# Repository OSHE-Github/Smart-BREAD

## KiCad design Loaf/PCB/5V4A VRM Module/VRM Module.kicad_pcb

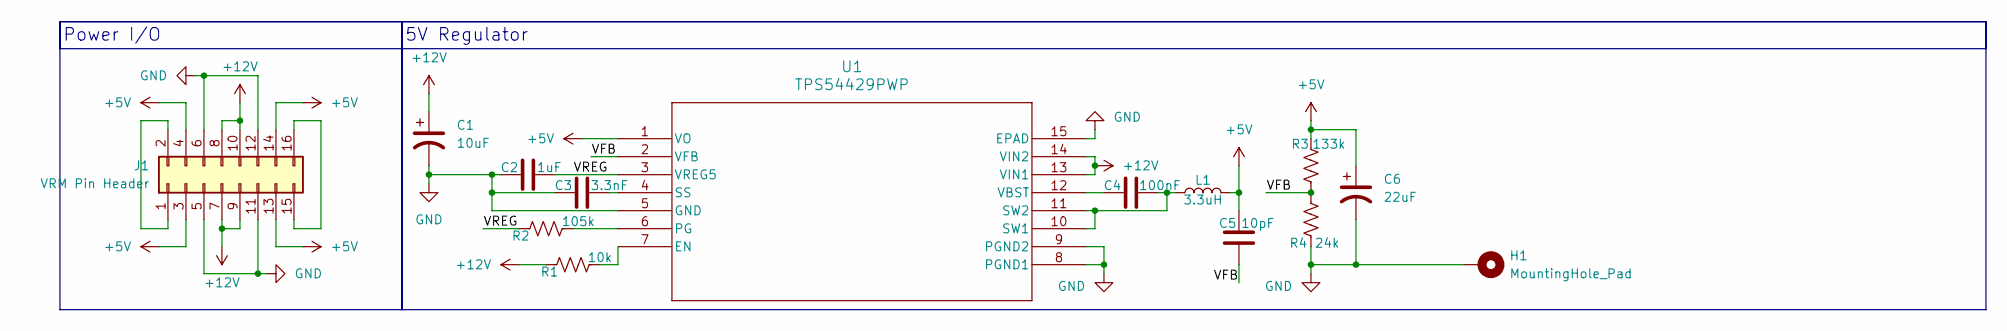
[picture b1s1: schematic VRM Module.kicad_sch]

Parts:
C1: 10uF; CP_Radial_D5.0mm_P2.50mm
C2: 1uF; C_1206_3216Metric_Pad1.33x1.80mm_HandSolder
C3: 3.3nF; C_1206_3216Metric_Pad1.33x1.80mm_HandSolder
C4: 100nF; C_1206_3216Metric_Pad1.33x1.80mm_HandSolder
C5: 10pF; C_1206_3216Metric_Pad1.33x1.80mm_HandSolder
C6: 22uF; CP_Radial_D5.0mm_P2.50mm
H1: MountingHole_Pad; MountingHole_3.2mm_M3_DIN965_Pad
J1: VRM Pin Header; PinHeader_2x08_P2.54mm_Vertical
L1: 3.3uH; R_1206_3216Metric_Pad1.30x1.75mm_HandSolder
R1: 10k; R_1206_3216Metric_Pad1.30x1.75mm_HandSolder
R2: 105k; R_1206_3216Metric_Pad1.30x1.75mm_HandSolder
R3: 133k; R_1206_3216Metric_Pad1.30x1.75mm_HandSolder
R4: 24k; R_1206_3216Metric_Pad1.30x1.75mm_HandSolder
U1: TPS54429PWP; Texas_HTSSOP-14-1EP_4.4x5mm_P0.65mm_EP3.4x5mm_Mask2.94x3.34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

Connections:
+5V: C5.2, C6.1, J1.3, J1.4, J1.13, J1.14, L1.2, R3.2, U1.1 (VO)
+12V: C1.1, J1.7, J1.8, J1.9, J1.10, R1.1, U1.13 (VIN1), U1.14 (VIN2)
/VFB: C5.1, R3.1, R4.2, U1.2 (VFB)
/VREG: C2.2, R2.1, U1.3 (VREG5)
GND: C1.2, C2.1, C3.1, C6.2, H1.1 (1_1), J1.5, J1.6, J1.11, J1.12, R4.1, U1.5 (GND), U1.8 (PGND1), U1.9 (PGND2), U1.15 (EPAD)
unnamed: J1.1, J1.2
unnamed: J1.15, J1.16
unnamed: R1.2, U1.7 (EN)
unnamed: R2.2, U1.6 (PG)
unnamed: C3.2, U1.4 (SS)
unnamed: C4.2, L1.1, U1.10 (SW1), U1.11 (SW2)
unnamed: C4.1, U1.12 (VBST)

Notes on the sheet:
5V Regulator
Power I/O

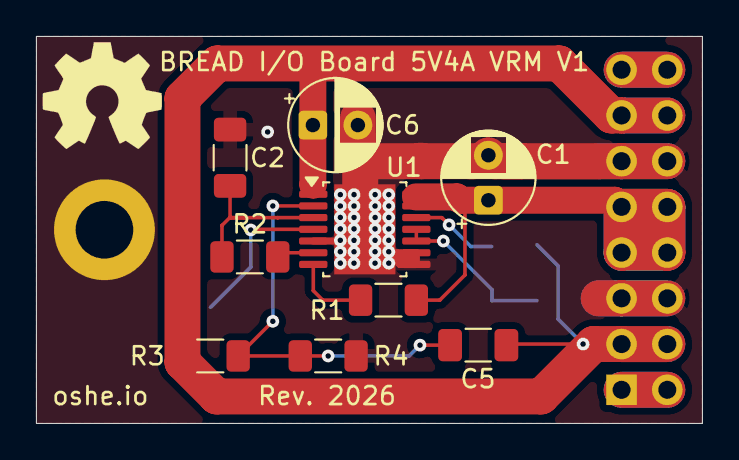
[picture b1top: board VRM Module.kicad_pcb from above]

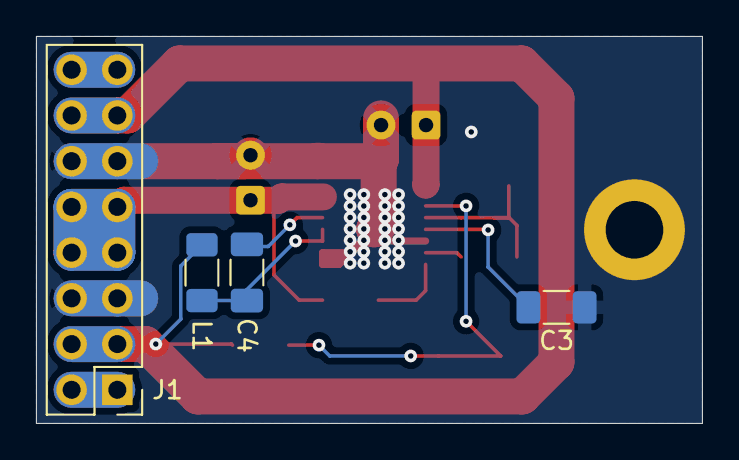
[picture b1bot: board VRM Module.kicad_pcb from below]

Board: 2 copper layers, 37.0 x 21.5 mm, 15 parts (5 on the bottom side), 12 nets.

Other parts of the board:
Logo1: Logo_Open_Hardware_Small; OSHW-Symbol_6.7x6mm_SilkScreen

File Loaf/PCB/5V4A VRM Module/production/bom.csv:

Designator,Footprint,Quantity,Value,LCSC Part #
C1,CP_Radial_D5.0mm_P2.50mm,1,10uF,
C2,1206,1,1uF,
C3,1206,1,3.3uF,
C4,1206,1,100nF,
C5,1206,1,10pF,
C6,CP_Radial_D5.0mm_P2.50mm,1,22uF,
J1,PinHeader_2x08_P2.54mm_Vertical,1,VRM Pin Header,
L1,1206,1,3.3uH,
LOGO1,OSHW-Symbol_6.7x6mm_SilkScreen,1,Logo_Open_Hardware_Small,
R1,1206,1,10k,
R2,1206,1,105k,
R3,1206,1,133k,
R4,1206,1,24k,
U1,Texas_HTSSOP-14-1EP_4.4x5mm_P0.65mm_EP3.4x5mm_Mask2.94x3.34mm,1,TPS54429PWP,

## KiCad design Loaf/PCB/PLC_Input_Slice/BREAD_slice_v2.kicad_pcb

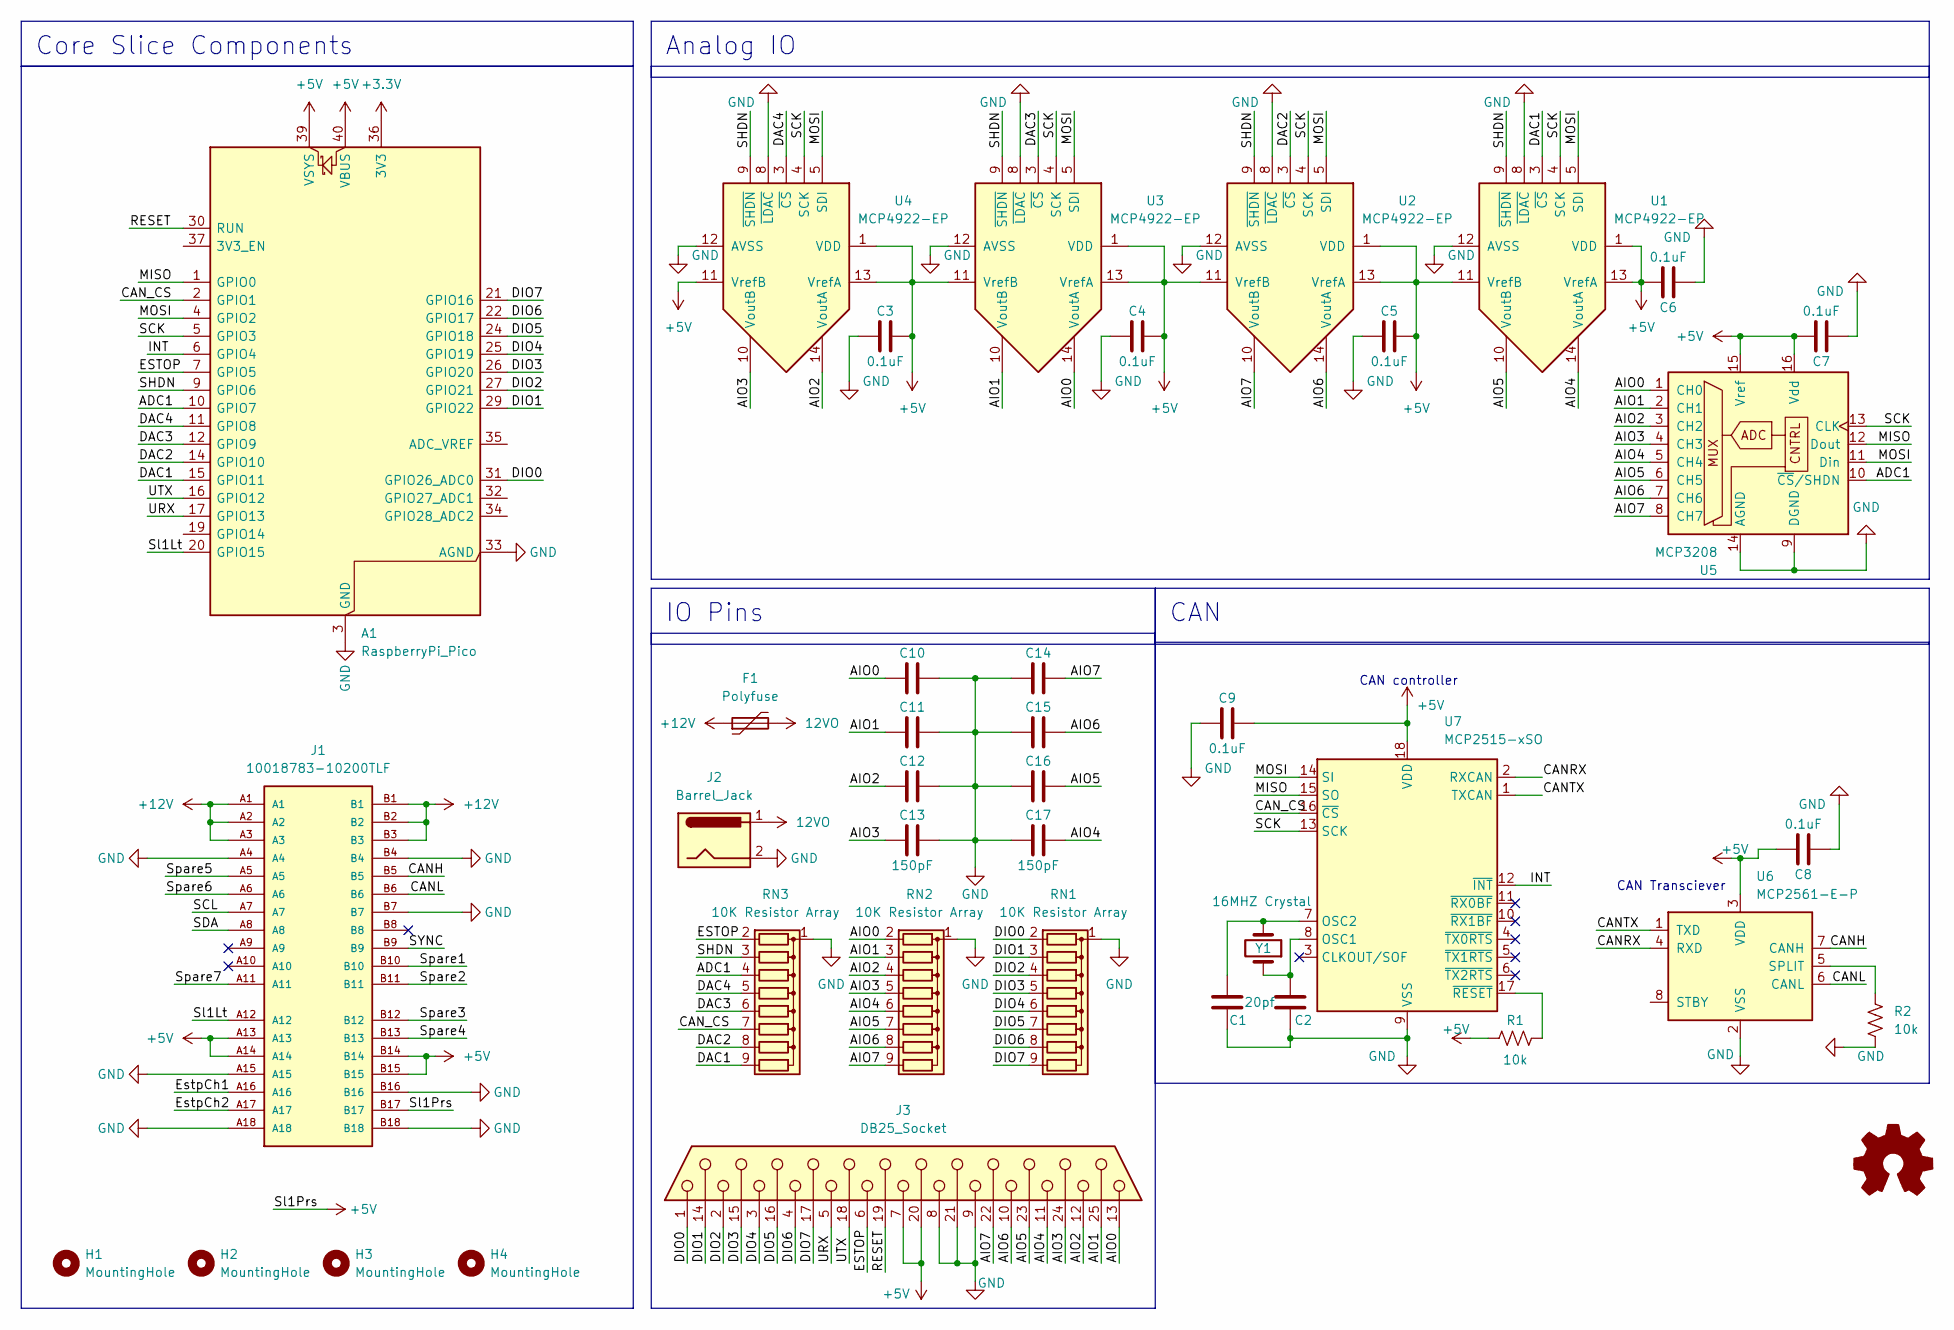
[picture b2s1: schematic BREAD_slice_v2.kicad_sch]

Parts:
A1: RaspberryPi_Pico; RaspberryPi_Pico_Common_Unspecified
C1, C2: 20pf; C_1206_3216Metric_Pad1.33x1.80mm_HandSolder
C3, C4, C5, C6, C7, C8, C9: 0.1uF; C_1206_3216Metric_Pad1.33x1.80mm_HandSolder
C10, C11, C12, C13, C14, C15, C16, C17: 150pF; C_1206_3216Metric_Pad1.33x1.80mm_HandSolder
F1: Polyfuse; Fuse_2920_7451Metric_Pad2.10x5.45mm_HandSolder
H1, H2, H3, H4: MountingHole; MountingHole_3.2mm_M3_DIN965_Pad
J1: 10018783-10200TLF; BUS_PCIexpress_x1; PARTREV Z
J2: Barrel_Jack; BarrelJack_CUI_PJ-063AH_Horizontal
J3: DB25_Socket; DSUB-25_Socket_Horizontal_P2.77x2.84mm_EdgePinOffset4.94mm_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
Logo1: Logo_Open_Hardware_Small; OSHW-Symbol_6.7x6mm_SilkScreen
R1, R2: 10k; R_1206_3216Metric_Pad1.30x1.75mm_HandSolder
RN1, RN2, RN3: 10K Resistor Array; R_Array_SIP9
U1, U2, U3, U4: MCP4922-EP; DIP-14_W7.62mm
U5: MCP3208; DIP-16_W7.62mm_LongPads
U6: MCP2561-E-P; DIP-8_W7.62mm
U7: MCP2515-xSO; DIP-18_W7.62mm
Y1: 16MHZ Crystal; Crystal_HC49-4H_Vertical

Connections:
12VO: F1.2, J2.1
+3.3V: A1.36 (3V3)
+5V: A1.39 (VSYS), A1.40 (VBUS), C3.2, C4.2, C5.2, C6.2, C7.2, C8.2, C9.2, J1.A13, J1.A14, J1.B14, J1.B15, J1.B17, J3.7, J3.20, R1.2, U1.1 (VDD), U1.11 (VrefB), U1.13 (VrefA), U2.1 (VDD), U2.11 (VrefB), U2.13 (VrefA), U3.1 (VDD), U3.11 (VrefB), U3.13 (VrefA), U4.1 (VDD), U4.11 (VrefB), U4.13 (VrefA), U5.15 (Vref), U5.16 (Vdd), U6.3 (VDD), U7.18 (VDD)
+12V: F1.1, J1.A1, J1.A2, J1.A3, J1.B1, J1.B2, J1.B3
/ADC1: A1.10 (GPIO7), RN3.4 (R3), U5.10 (~CS/SHDN)
/AIO0: C10.1, J3.13, RN2.2 (R1), U3.14 (VoutA), U5.1 (CH0)
/AIO1: C11.1, J3.25, RN2.3 (R2), U3.10 (VoutB), U5.2 (CH1)
/AIO2: C12.1, J3.12, RN2.4 (R3), U4.14 (VoutA), U5.3 (CH2)
/AIO3: C13.1, J3.24, RN2.5 (R4), U4.10 (VoutB), U5.4 (CH3)
/AIO4: C17.2, J3.11, RN2.6 (R5), U1.14 (VoutA), U5.5 (CH4)
/AIO5: C16.2, J3.23, RN2.7 (R6), U1.10 (VoutB), U5.6 (CH5)
/AIO6: C15.2, J3.10, RN2.8 (R7), U2.14 (VoutA), U5.7 (CH6)
/AIO7: C14.2, J3.22, RN2.9 (R8), U2.10 (VoutB), U5.8 (CH7)
/CANH: J1.B5, U6.7 (CANH)
/CANL: J1.B6, U6.6 (CANL)
/CANRX: U6.4 (RXD), U7.2 (RXCAN)
/CANTX: U6.1 (TXD), U7.1 (TXCAN)
/CAN_CS: A1.2 (GPIO1), RN3.7 (R6), U7.16 (~CS)
/DAC1: A1.15 (GPIO11), RN3.9 (R8), U1.3 (~CS)
/DAC2: A1.14 (GPIO10), RN3.8 (R7), U2.3 (~CS)
/DAC3: A1.12 (GPIO9), RN3.6 (R5), U3.3 (~CS)
/DAC4: A1.11 (GPIO8), RN3.5 (R4), U4.3 (~CS)
/DIO0: A1.31 (GPIO26_ADC0), J3.1, RN1.2 (R1)
/DIO1: A1.29 (GPIO22), J3.14, RN1.3 (R2)
/DIO2: A1.27 (GPIO21), J3.2, RN1.4 (R3)
/DIO3: A1.26 (GPIO20), J3.15, RN1.5 (R4)
/DIO4: A1.25 (GPIO19), J3.3, RN1.6 (R5)
/DIO5: A1.24 (GPIO18), J3.16, RN1.7 (R6)
/DIO6: A1.22 (GPIO17), J3.4, RN1.8 (R7)
/DIO7: A1.21 (GPIO16), J3.17, RN1.9 (R8)
/ESTOP: A1.7 (GPIO5), J3.6, RN3.2 (R1)
/EstpCh1: J1.A16
/EstpCh2: J1.A17
/INT: A1.6 (GPIO4), U7.12 (~INT)
/MISO: A1.1 (GPIO0), U5.12 (Dout), U7.15 (SO)
/MOSI: A1.4 (GPIO2), U1.5 (SDI), U2.5 (SDI), U3.5 (SDI), U4.5 (SDI), U5.11 (Din), U7.14 (SI)
/RESET: A1.30 (RUN), J3.19
/SCK: A1.5 (GPIO3), U1.4 (SCK), U2.4 (SCK), U3.4 (SCK), U4.4 (SCK), U5.13 (CLK), U7.13 (SCK)
/SCL: J1.A7
/SDA: J1.A8
/SHDN: A1.9 (GPIO6), RN3.3 (R2), U1.9 (~SHDN), U2.9 (~SHDN), U3.9 (~SHDN), U4.9 (~SHDN)
/SYNC: J1.B9
/Sl1Lt: A1.20 (GPIO15), J1.A12
/Spare1: J1.B10
/Spare2: J1.B11
/Spare3: J1.B12
/Spare4: J1.B13
/Spare5: J1.A5
/Spare6: J1.A6
/Spare7: J1.A11
/URX: A1.17 (GPIO13), J3.5
/UTX: A1.16 (GPIO12), J3.18
GND: A1.3 (GND), A1.8 (GND), A1.13 (GND), A1.18 (GND), A1.23 (GND), A1.28 (GND), A1.33 (AGND), A1.38 (GND), C1.2, C2.2, C3.1, C4.1, C5.1, C6.1, C7.1, C8.1, C9.1, C10.2, C11.2, C12.2, C13.2, C14.1, C15.1, C16.1, C17.1, J1.A4, J1.A15, J1.A18, J1.B4, J1.B7, J1.B16, J1.B18, J2.2, J3.8, J3.9, J3.21, R2.1, RN1.1 (common), RN2.1 (common), RN3.1 (common), U1.8 (~LDAC), U1.12 (AVSS), U2.8 (~LDAC), U2.12 (AVSS), U3.8 (~LDAC), U3.12 (AVSS), U4.8 (~LDAC), U4.12 (AVSS), U5.9 (DGND), U5.14 (AGND), U6.2 (VSS), U7.9 (VSS)
unnamed: R2.2, U6.5 (SPLIT)
unnamed: C2.1, U7.8 (OSC1), Y1.1
unnamed: C1.1, U7.7 (OSC2), Y1.2
unnamed: R1.1, U7.17 (~RESET)

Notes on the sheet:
CAN Transciever
CAN controller
CAN
IO Pins
Analog IO
Core Slice Components

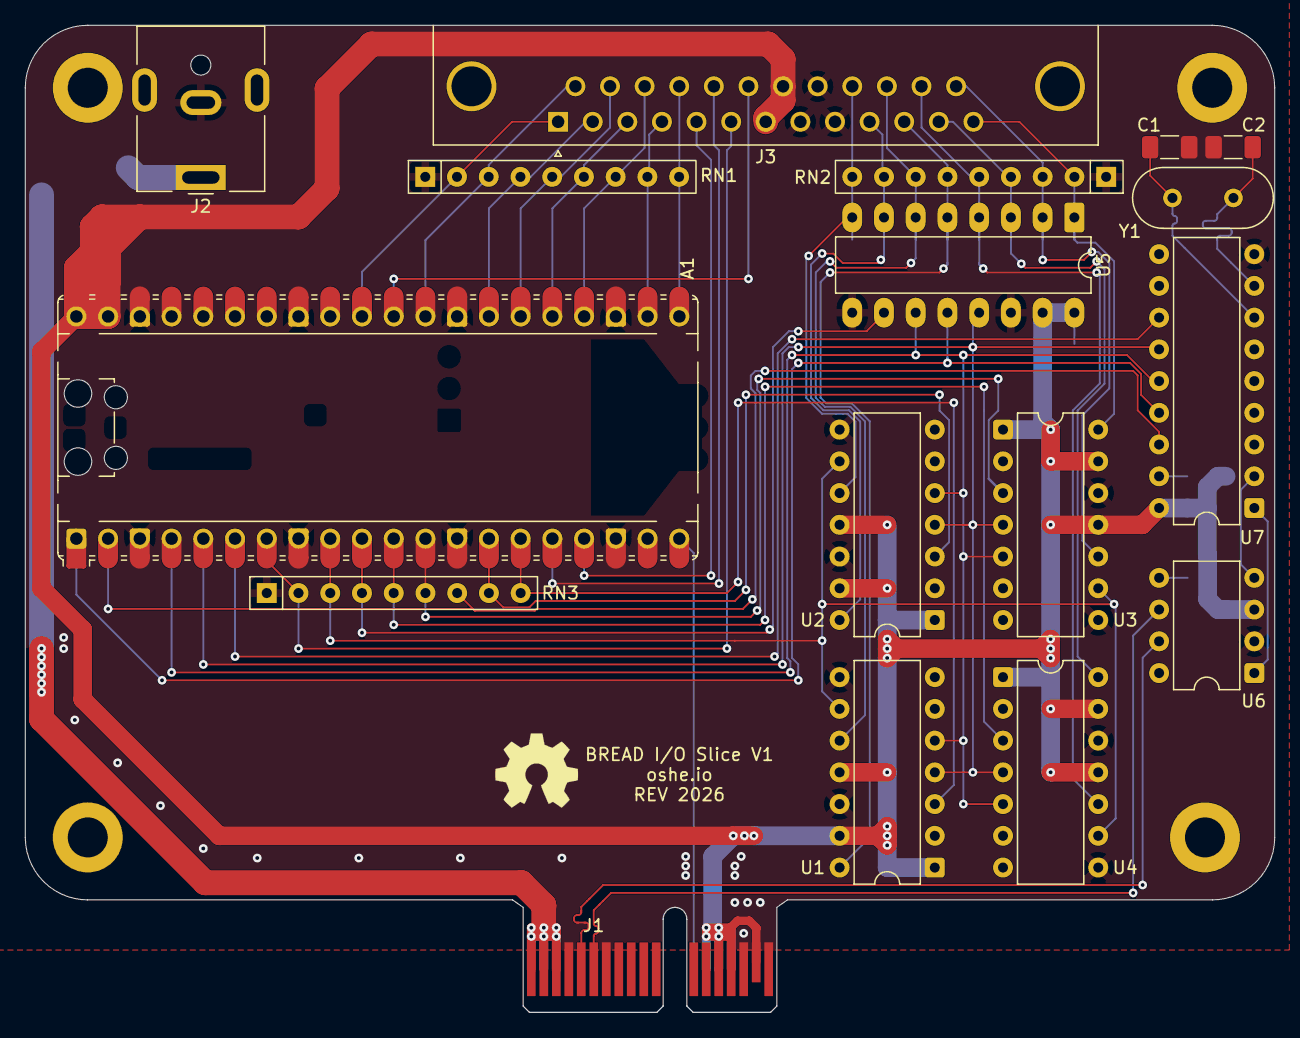
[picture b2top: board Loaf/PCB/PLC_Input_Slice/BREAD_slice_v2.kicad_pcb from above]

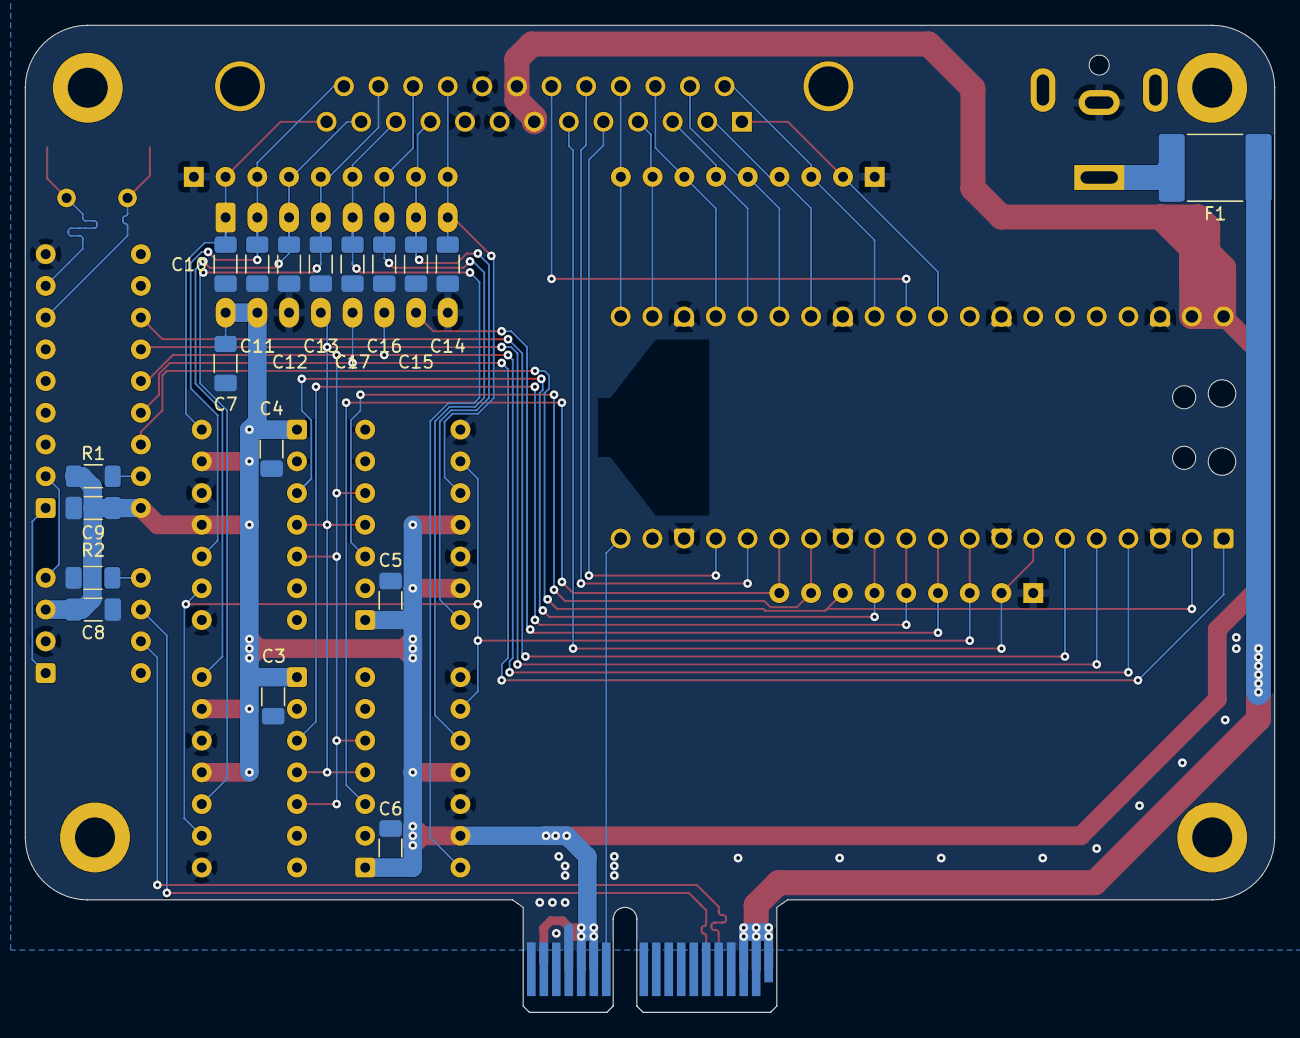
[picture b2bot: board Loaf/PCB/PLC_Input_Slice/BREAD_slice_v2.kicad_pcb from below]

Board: 2 copper layers, 100.0 x 79.0 mm, 40 parts (22 on the bottom side), 44 nets.

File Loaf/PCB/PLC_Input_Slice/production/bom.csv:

Designator,Footprint,Quantity,Value,LCSC Part #
A1,RaspberryPi_Pico_Common_Unspecified,1,RaspberryPi_Pico,
"C1, C2",1206,2,20pf,
"C10, C11, C12, C13, C14, C15, C16, C17",1206,8,150pF,
"C3, C4, C5, C6, C7, C8, C9",1206,7,0.1uF,
F1,2920,1,Polyfuse,
J1,BUS_PCIexpress_x1,1,10018783-10200TLF,
J2,BarrelJack_CUI_PJ-063AH_Horizontal,1,Barrel_Jack,
J3,DSUB-25_Socket_Horizontal_P2.77x2.84mm_EdgePinOffset4.94mm_Housed_MountingHolesOffset4.94mm,1,DB25_Socket,
LOGO1,OSHW-Symbol_6.7x6mm_SilkScreen,1,Logo_Open_Hardware_Small,
"R1, R2",1206,2,10k,
"RN1, RN2, RN3",R_Array_SIP9,3,10K Resistor Array,
"U1, U2, U3, U4",DIP-14_W7.62mm,4,MCP4922-EP,
U5,DIP-16_W7.62mm_LongPads,1,MCP3208,
U6,DIP-8_W7.62mm,1,MCP2561-E-P,
U7,DIP-18_W7.62mm,1,MCP2515-xSO,
Y1,Crystal_HC49-4H_Vertical,1,16MHZ Crystal,

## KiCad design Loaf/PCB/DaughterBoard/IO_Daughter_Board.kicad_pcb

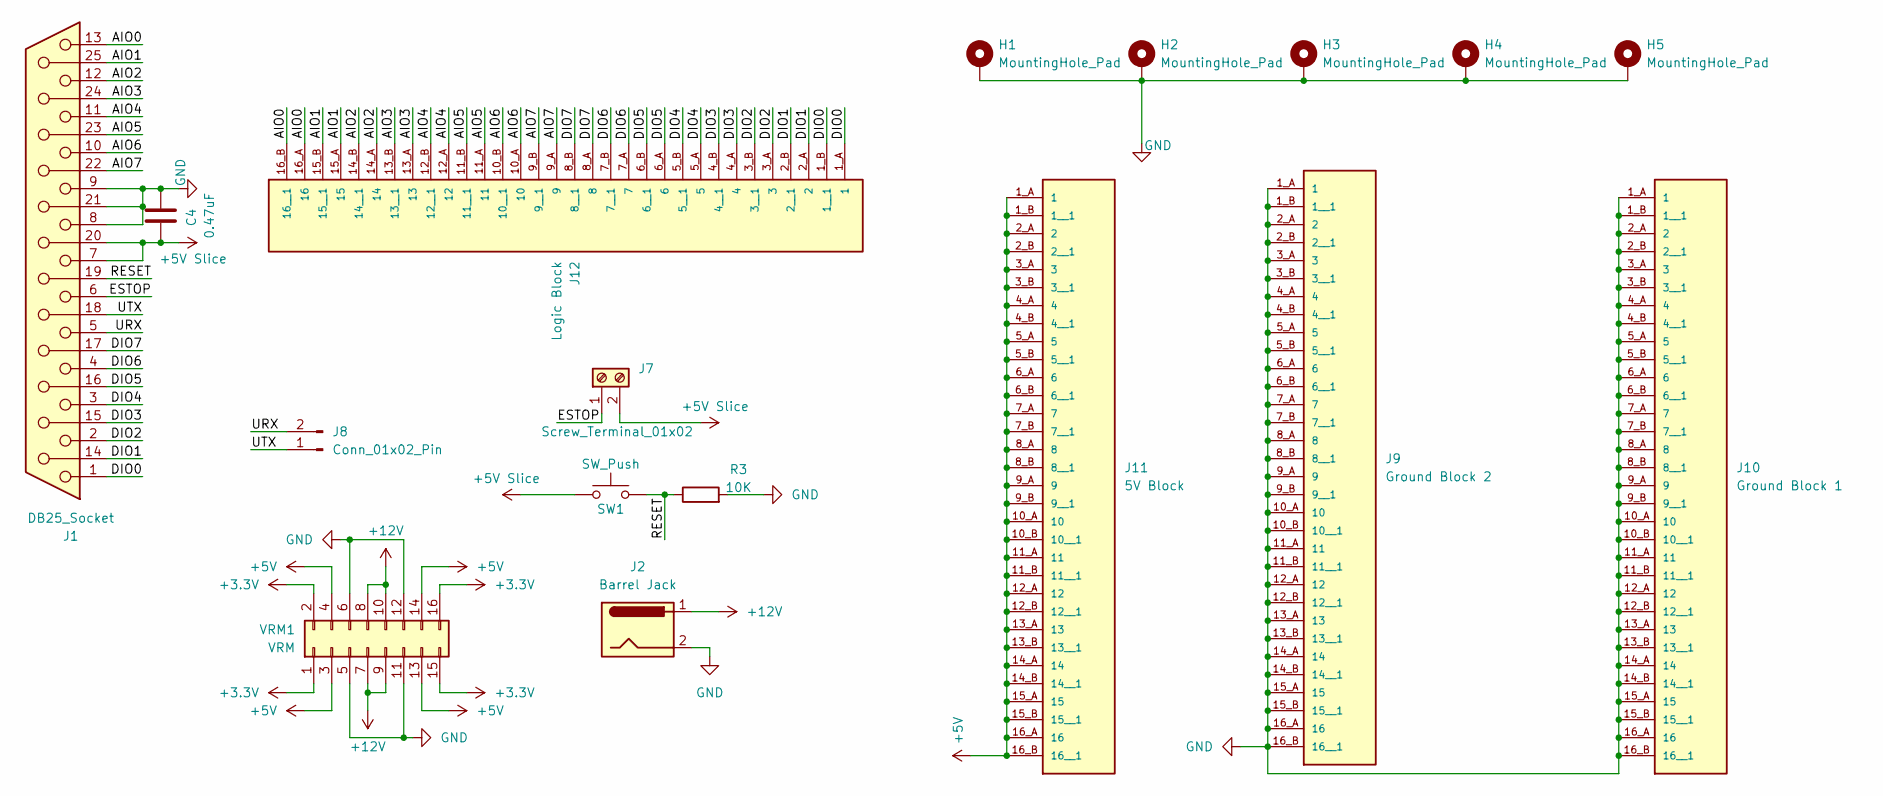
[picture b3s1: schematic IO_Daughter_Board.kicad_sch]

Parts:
C4: 0.47uF; C_1206_3216Metric_Pad1.33x1.80mm_HandSolder
H1, H2, H3, H4, H5: MountingHole_Pad; MountingHole_3.2mm_M3_DIN965_Pad
J1: DB25_Socket; DSUB-25_Socket_Horizontal_P2.77x2.84mm_EdgePinOffset4.94mm_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
J2: Barrel Jack; BarrelJack_CUI_PJ-063AH_Horizontal
J7: Screw_Terminal_01x02; TerminalBlock_MaiXu_MX126-5.0-02P_1x02_P5.00mm
J8: Conn_01x02_Pin; PinHeader_1x02_P2.54mm_Horizontal
J9: Ground Block 2; CUI_TBL009-254-16GY-2GY
J10: Ground Block 1; CUI_TBL009-254-16GY-2GY
J11: 5V Block; CUI_TBL009-254-16GY-2GY
J12: Logic Block; CUI_TBL009-254-16GY-2GY
R3: 10K; R_Axial_DIN0204_L3.6mm_D1.6mm_P7.62mm_Horizontal
SW1: SW_Push; SW_Tactile_Straight_KSL0Axx1LFTR
VRM1: VRM; PinSocket_2x08_P2.54mm_Vertical

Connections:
+3.3V: VRM1.1, VRM1.2, VRM1.15, VRM1.16
+5V: J11.1_A (1), J11.1_B (1__1), J11.2_A (2), J11.2_B (2__1), J11.3_A (3), J11.3_B (3__1), J11.4_A (4), J11.4_B (4__1), J11.5_A (5), J11.5_B (5__1), J11.6_A (6), J11.6_B (6__1), J11.7_A (7), J11.7_B (7__1), J11.8_A (8), J11.8_B (8__1), J11.9_A (9), J11.9_B (9__1), J11.10_A (10), J11.10_B (10__1), J11.11_A (11), J11.11_B (11__1), J11.12_A (12), J11.12_B (12__1), J11.13_A (13), J11.13_B (13__1), J11.14_A (14), J11.14_B (14__1), J11.15_A (15), J11.15_B (15__1), J11.16_A (16), J11.16_B (16__1), VRM1.3, VRM1.4, VRM1.13, VRM1.14
+5V Slice: C4.1, J1.7, J1.20, J7.2, SW1.1
+12V: J2.1, VRM1.7, VRM1.8, VRM1.9, VRM1.10
/AIO0: J1.13, J12.16_A (16), J12.16_B (16__1)
/AIO1: J1.25, J12.15_A (15), J12.15_B (15__1)
/AIO2: J1.12, J12.14_A (14), J12.14_B (14__1)
/AIO3: J1.24, J12.13_A (13), J12.13_B (13__1)
/AIO4: J1.11, J12.12_A (12), J12.12_B (12__1)
/AIO5: J1.23, J12.11_A (11), J12.11_B (11__1)
/AIO6: J1.10, J12.10_A (10), J12.10_B (10__1)
/AIO7: J1.22, J12.9_A (9), J12.9_B (9__1)
/DIO0: J1.1, J12.1_A (1), J12.1_B (1__1)
/DIO1: J1.14, J12.2_A (2), J12.2_B (2__1)
/DIO2: J1.2, J12.3_A (3), J12.3_B (3__1)
/DIO3: J1.15, J12.4_A (4), J12.4_B (4__1)
/DIO4: J1.3, J12.5_A (5), J12.5_B (5__1)
/DIO5: J1.16, J12.6_A (6), J12.6_B (6__1)
/DIO6: J1.4, J12.7_A (7), J12.7_B (7__1)
/DIO7: J1.17, J12.8_A (8), J12.8_B (8__1)
/ESTOP: J1.6, J7.1
/RESET: J1.19, R3.1, SW1.2
/URX: J1.5, J8.2
/UTX: J1.18, J8.1
GND: C4.2, H1.1 (1_1), H2.1 (1_1), H3.1 (1_1), H4.1 (1_1), H5.1 (1_1), J1.8, J1.9, J1.21, J2.2, J9.1_A (1), J9.1_B (1__1), J9.2_A (2), J9.2_B (2__1), J9.3_A (3), J9.3_B (3__1), J9.4_A (4), J9.4_B (4__1), J9.5_A (5), J9.5_B (5__1), J9.6_A (6), J9.6_B (6__1), J9.7_A (7), J9.7_B (7__1), J9.8_A (8), J9.8_B (8__1), J9.9_A (9), J9.9_B (9__1), J9.10_A (10), J9.10_B (10__1), J9.11_A (11), J9.11_B (11__1), J9.12_A (12), J9.12_B (12__1), J9.13_A (13), J9.13_B (13__1), J9.14_A (14), J9.14_B (14__1), J9.15_A (15), J9.15_B (15__1), J9.16_A (16), J9.16_B (16__1), J10.1_A (1), J10.1_B (1__1), J10.2_A (2), J10.2_B (2__1), J10.3_A (3), J10.3_B (3__1), J10.4_A (4), J10.4_B (4__1), J10.5_A (5), J10.5_B (5__1), J10.6_A (6), J10.6_B (6__1), J10.7_A (7), J10.7_B (7__1), J10.8_A (8), J10.8_B (8__1), J10.9_A (9), J10.9_B (9__1), J10.10_A (10), J10.10_B (10__1), J10.11_A (11), J10.11_B (11__1), J10.12_A (12), J10.12_B (12__1), J10.13_A (13), J10.13_B (13__1), J10.14_A (14), J10.14_B (14__1), J10.15_A (15), J10.15_B (15__1), J10.16_A (16), J10.16_B (16__1), R3.2, VRM1.5, VRM1.6, VRM1.11, VRM1.12

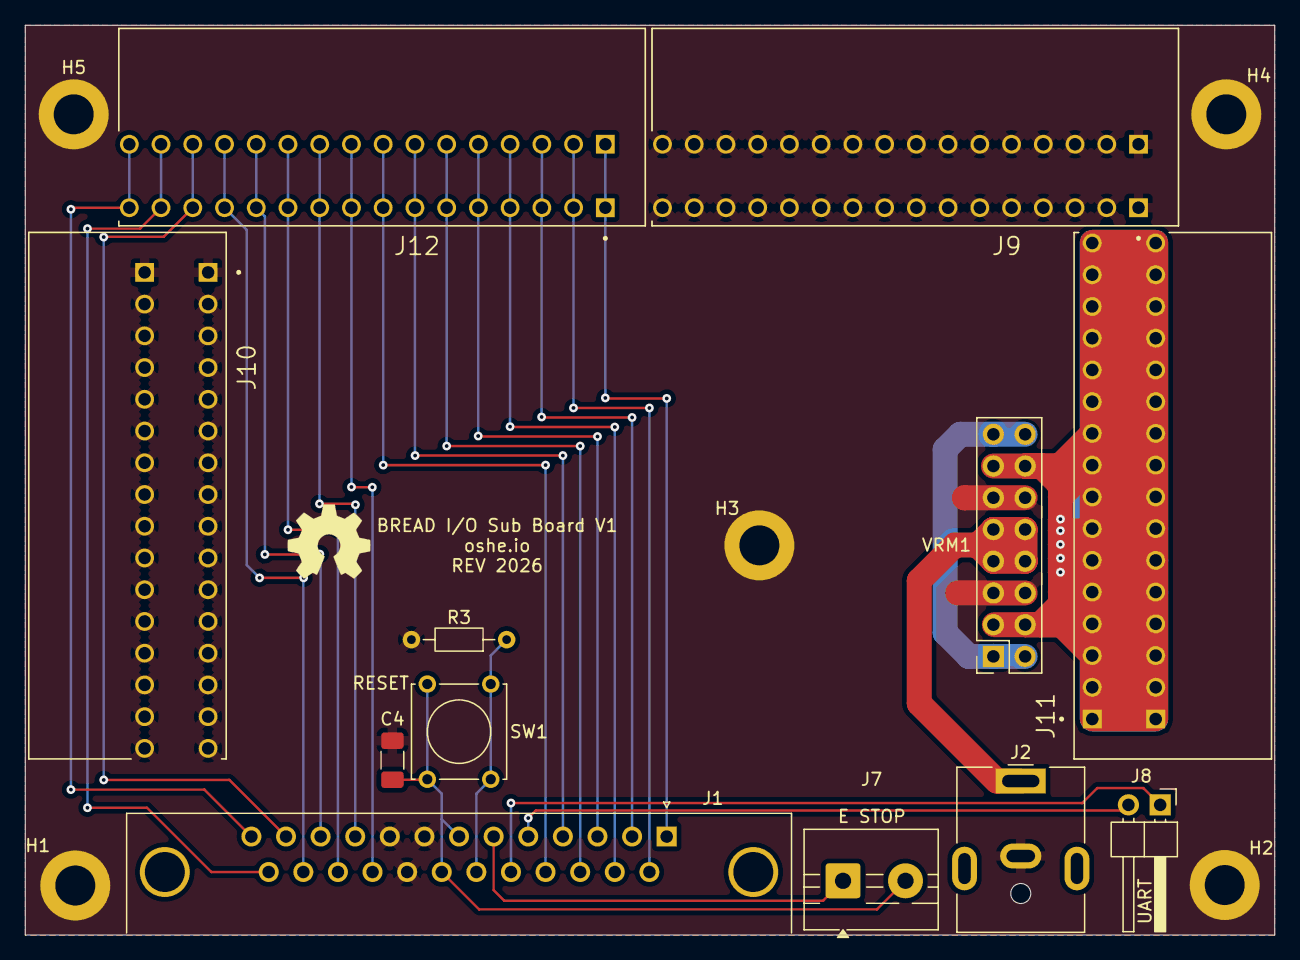
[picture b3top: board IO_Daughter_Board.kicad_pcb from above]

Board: 2 copper layers, 100.0 x 72.8 mm, 18 parts (0 on the bottom side), 25 nets.

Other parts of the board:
Logo1: Logo_Open_Hardware_Small; OSHW-Symbol_6.7x6mm_SilkScreen

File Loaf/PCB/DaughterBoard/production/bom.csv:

Designator,Footprint,Quantity,Value,LCSC Part #
C4,1206,1,0.47uF,
J1,DSUB-25_Socket_Horizontal_P2.77x2.84mm_EdgePinOffset4.94mm_Housed_MountingHolesOffset4.94mm,1,DB25_Socket,
J10,CUI_TBL009-254-16GY-2GY,1,Ground Block 1,
J11,CUI_TBL009-254-16GY-2GY,1,5V Block,
J12,CUI_TBL009-254-16GY-2GY,1,Logic Block,
J2,BarrelJack_CUI_PJ-063AH_Horizontal,1,Barrel Jack,
J7,TerminalBlock_MaiXu_MX126-5.0-02P_1x02_P5.00mm,1,Screw_Terminal_01x02,
J8,PinHeader_1x02_P2.54mm_Horizontal,1,Conn_01x02_Pin,
J9,CUI_TBL009-254-16GY-2GY,1,Ground Block 2,
LOGO1,OSHW-Symbol_6.7x6mm_SilkScreen,1,Logo_Open_Hardware_Small,
R3,R_Axial_DIN0204_L3.6mm_D1.6mm_P7.62mm_Horizontal,1,10K,
SW1,SW_Tactile_Straight_KSL0Axx1LFTR,1,SW_Push,
VRM1,PinSocket_2x08_P2.54mm_Vertical,1,VRM,

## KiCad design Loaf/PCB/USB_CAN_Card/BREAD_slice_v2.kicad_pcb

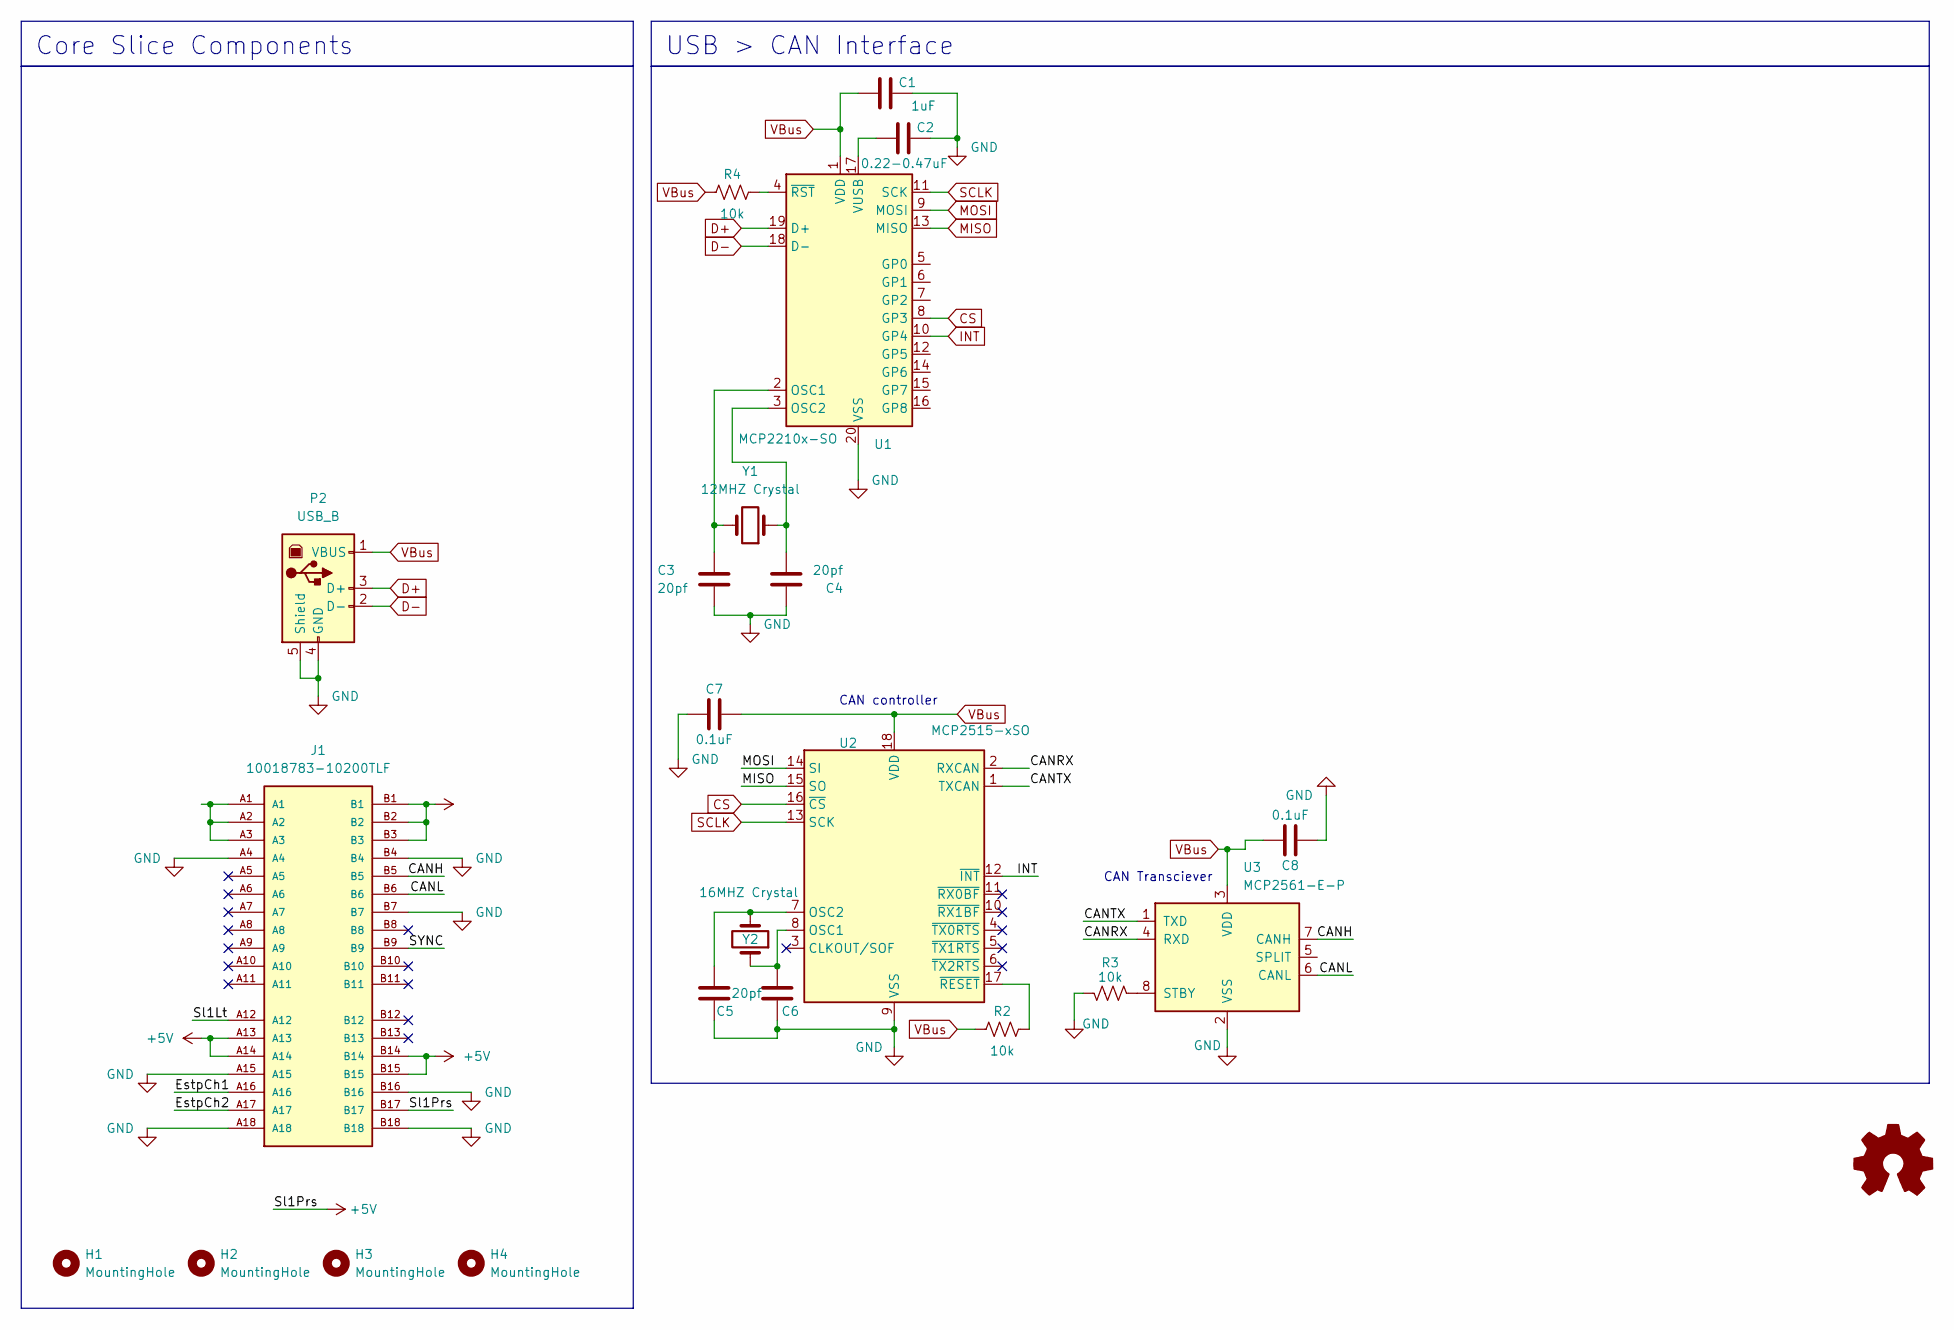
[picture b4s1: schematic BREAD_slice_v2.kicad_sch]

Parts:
C1: 1uF; C_1206_3216Metric_Pad1.33x1.80mm_HandSolder
C2: 0.22-0.47uF; C_1206_3216Metric_Pad1.33x1.80mm_HandSolder
C3, C4, C5, C6: 20pf; C_1206_3216Metric_Pad1.33x1.80mm_HandSolder
C7, C8: 0.1uF; C_1206_3216Metric_Pad1.33x1.80mm_HandSolder
H1, H2, H3, H4: MountingHole; MountingHole_3.2mm_M3_DIN965_Pad
J1: 10018783-10200TLF; BUS_PCIexpress_x1; PARTREV Z
Logo1: Logo_Open_Hardware_Small; OSHW-Symbol_6.7x6mm_SilkScreen
P2: USB_B; USB_B_OST_USB-B1HSxx_Horizontal
R2, R3, R4: 10k; R_1206_3216Metric_Pad1.30x1.75mm_HandSolder
U1: MCP2210x-SO; SOIC-20W_7.5x12.8mm_P1.27mm
U2: MCP2515-xSO; DIP-18_W7.62mm
U3: MCP2561-E-P; DIP-8_W7.62mm
Y1: 12MHZ Crystal; Crystal_HC49-4H_Vertical
Y2: 16MHZ Crystal; Crystal_HC49-4H_Vertical

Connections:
+5V: J1.A13, J1.A14, J1.B14, J1.B15, J1.B17
+12V: J1.B1, J1.B2, J1.B3
/CANH: J1.B5, U3.7 (CANH)
/CANL: J1.B6, U3.6 (CANL)
/CANRX: U2.2 (RXCAN), U3.4 (RXD)
/CANTX: U2.1 (TXCAN), U3.1 (TXD)
/EstpCh1: J1.A16
/EstpCh2: J1.A17
/SYNC: J1.B9
/Sl1Lt: J1.A12
CS: U1.8 (GP3), U2.16 (~CS)
D+: P2.3 (D+), U1.19 (D+)
D-: P2.2 (D-), U1.18 (D-)
GND: C1.1, C2.1, C3.2, C4.1, C5.2, C6.2, C7.1, C8.1, J1.A4, J1.A15, J1.A18, J1.B4, J1.B7, J1.B16, J1.B18, P2.4 (GND), P2.5 (Shield), R3.2, U1.20 (VSS), U2.9 (VSS), U3.2 (VSS)
INT: U1.10 (GP4), U2.12 (~INT)
MISO: U1.13 (MISO), U2.15 (SO)
MOSI: U1.9 (MOSI), U2.14 (SI)
unnamed: J1.A1, J1.A2, J1.A3
unnamed: C3.1, U1.2 (OSC1), Y1.2
unnamed: C4.2, U1.3 (OSC2), Y1.1
unnamed: C2.2, U1.17 (VUSB)
unnamed: R4.1, U1.4 (~RST)
unnamed: C6.1, U2.8 (OSC1), Y2.1
unnamed: C5.1, U2.7 (OSC2), Y2.2
unnamed: R2.1, U2.17 (~RESET)
unnamed: R3.1, U3.8 (STBY)
SCLK: U1.11 (SCK), U2.13 (SCK)
VBus: C1.2, C7.2, C8.2, P2.1 (VBUS), R2.2, R4.2, U1.1 (VDD), U2.18 (VDD), U3.3 (VDD)

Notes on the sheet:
CAN controller
CAN Transciever
USB > CAN Interface
Core Slice Components
